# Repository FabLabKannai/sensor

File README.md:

FabLab Kannai Sensor Project
======

### Arduino Sensor Shield.
This shield have sensors below .<br>
- Temperature and humidity : DHT11<br>
- Air Pressure : MPL115A2<br>
- Light : NJL7502L<br>
- Noise : Condenser Microphone C9267<br>

Separately, requires the Arduino UNO and WiFi shield .<br>

## Sample code
Two types of Arduino sketch 
- Display the measured values on the PC with USB serial.
- Send the measured values to the server with WiFi shield.

Server side program
- Receive the measured values, and display on WEB site.

## Directries
arduino : Arduino sketch <br>
server : Server side program, PHP <br>
eagle : Board data, Eagle format <br>
case : Case data, Adobe illustrator format <br>
docs : Photos and documents <br>

## License
Souce code : Apache License 2.0<br>
Othes :  Creative Commons BY-SA

## Blog (in Japanese)
Sensor Project<br>
http://fablab-kannai.org/sensor_project <br>
Arduino Sensor Shield<br>
http://fablab-kannai.org/archives/787 <br>

## Photo

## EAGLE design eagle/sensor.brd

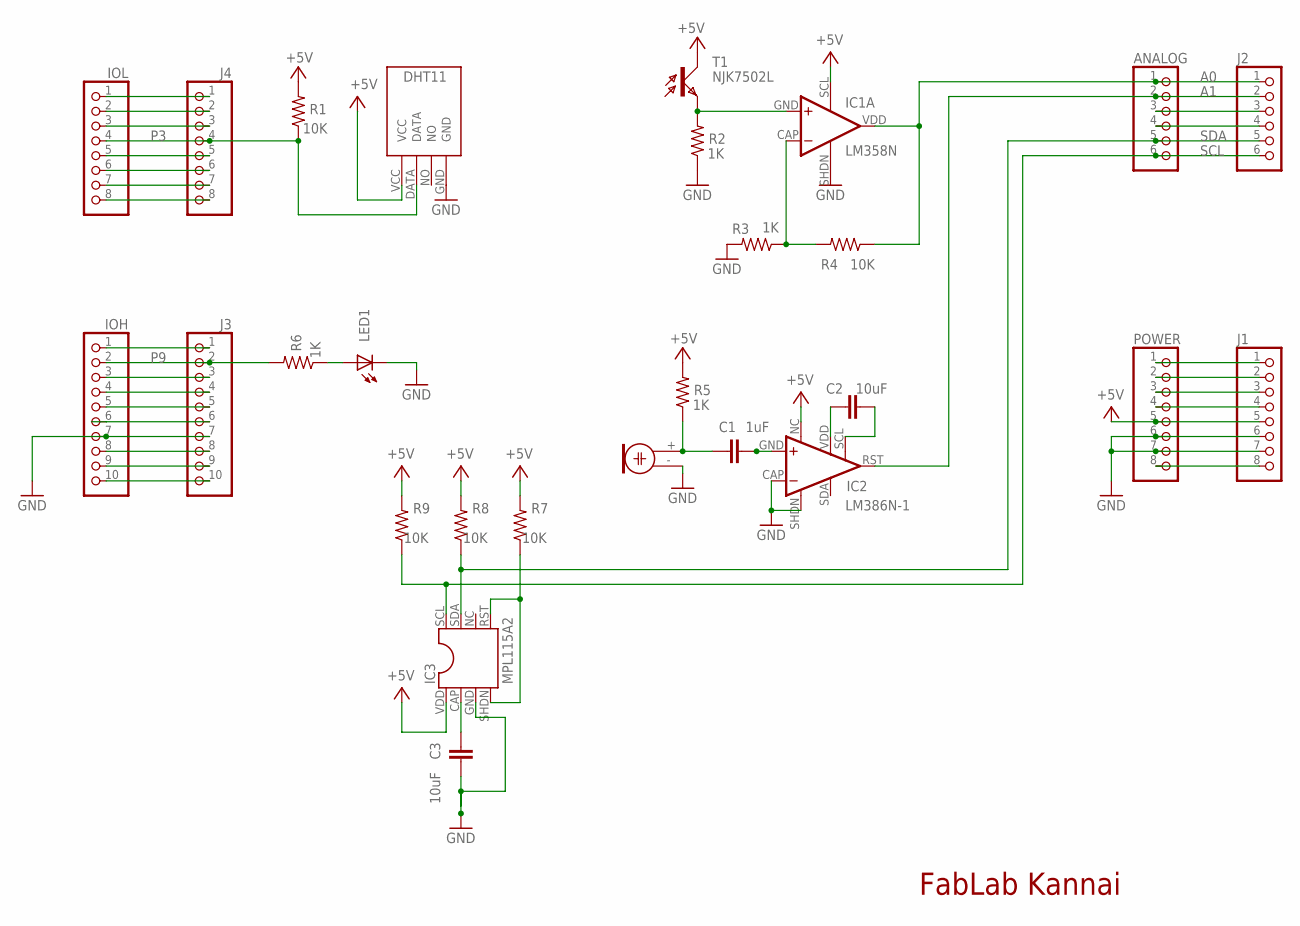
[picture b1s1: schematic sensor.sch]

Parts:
ANALOG: PINHD-1X6; 1X06
C1: 1uF; C025-025X050
C2, C3: 10uF; C025-025X050
IC1: LM358N; MPL115A2-DIL08
IC2: LM386N-1; MPL115A2-DIL08
IC3: MPL115A2; MPL115A2-DIL08
IOH: PINHD-1X10TH; 1X10-TH
IOL: PINHD-1X8TH; 1X08-TH
J1, J4: PINHD-1X8TH; 1X08-TH
J2: PINHD-1X6; 1X06
J3: PINHD-1X10TH; 1X10-TH
LED1: LED3MM
M1: C9257; DB-C9767
POWER: PINHD-1X8TH; 1X08-TH
R1, R4, R7, R8, R9: 10K; 0204/7
R2, R3, R5, R6: 1K; 0204/7
T1: NJK7502L; NJL7502L
U$1: DHT11

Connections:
+9V: J1.8, POWER.8
A0: ANALOG.1, IC1.VDD (OUT), J2.1, R4.1
A1: ANALOG.2, IC2.RST (OUT), J2.2
A2: ANALOG.3, J2.3
A3: ANALOG.4, J2.4
AREF: IOH.8, J3.8
GND: C3.2, IC1.SHDN (V-), IC2.CAP (-IN), IC2.SHDN (GND), IC3.GND, IOH.7, J1.6, J1.7, J3.7, LED1.K (C), M1.- (2), POWER.6, POWER.7, R2.1, R3.2, U$1.GND
unnamed: IOH.9, J3.9
unnamed: IOH.10, J3.10
unnamed: IC1.SCL (V+), IC2.NC (VS), IC3.VDD, J1.5, POWER.5, R1.2, R5.2, R7.2, R8.2, R9.2, T1.C, U$1.VCC
unnamed: IC1.GND (+IN), R2.2, T1.E
unnamed: IC3.RST, IC3.SHDN, R7.1
unnamed: IC1.CAP (-IN), R3.1, R4.2
unnamed: C3.1, IC3.CAP
unnamed: C2.1, IC2.VDD (GAIN)
unnamed: J1.2, POWER.2
unnamed: J1.1, POWER.1
unnamed: C1.2, IC2.GND (+IN)
unnamed: C2.2, IC2.SCL (GAIN)
unnamed: C1.1, M1.+ (1), R5.1
unnamed: LED1.A, R6.1
unnamed: J1.4, POWER.4
P0: IOL.1, J4.1
P1: IOL.2, J4.2
P2: IOL.3, J4.3
P3: IOL.4, J4.4, R1.1, U$1.DATA
P4: IOL.5, J4.5
P5: IOL.6, J4.6
P6: IOL.7, J4.7
P7: IOL.8, J4.8
P8: IOH.1, J3.1
P9: IOH.2, J3.2, R6.2
P10: IOH.3, J3.3
P11: IOH.4, J3.4
P12: IOH.5, J3.5
P13: IOH.6, J3.6
RESET: J1.3, POWER.3
SCL: ANALOG.6, IC3.SCL, J2.6, R9.1
SDA: ANALOG.5, IC3.SDA, J2.5, R8.1

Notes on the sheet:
FabLab Kannai

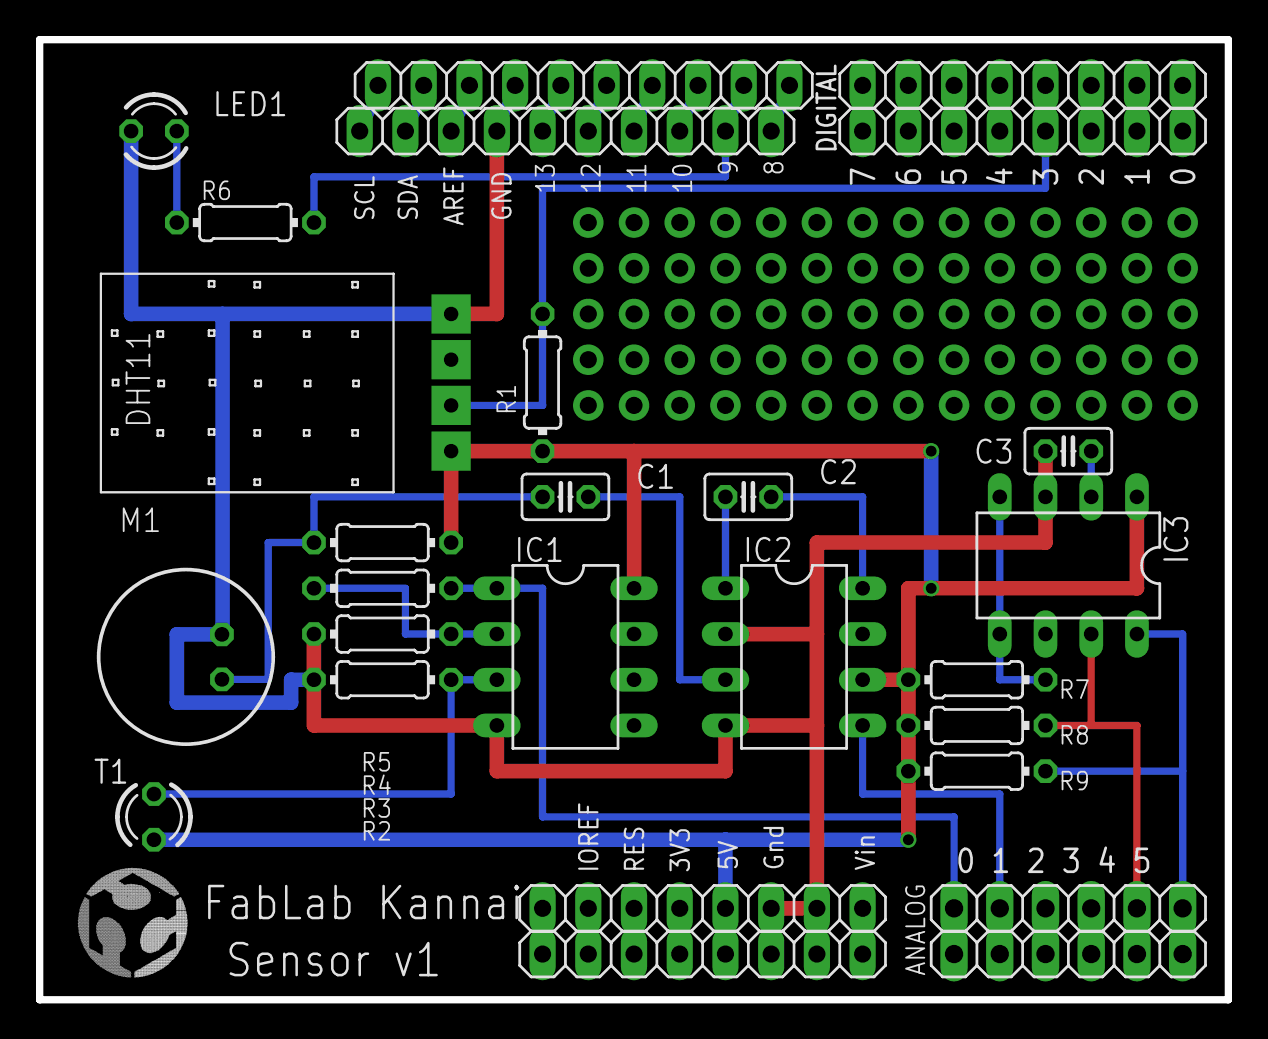
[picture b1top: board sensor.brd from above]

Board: 2 copper layers, 66.0 x 53.3 mm, 27 parts (0 on the bottom side), 39 nets.

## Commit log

2014-11-21 First Version
2014-11-22 FirstVersion
2015-02-16 case
